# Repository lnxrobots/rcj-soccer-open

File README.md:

# RoboCup Soccer Open

## Setup

### Install packages and libraries

```
sudo apt install python3-pip git i2c-tools python3-opencv python3-serial python3-websockets
```

```
sudo pip3 install Adafruit-Blinka adafruit-circuitpython-bno055 adafruit-extended-bus adafruit-circuitpython-ssd1306 pillow bluedot
```

### Enable software I2C and second UART, disable builtin Bluetooth

Add following lines to `/boot/config.txt`:

```
# Software i2c - custom
dtoverlay=i2c-gpio,bus=3

# Second and fifth UART - custom
dtoverlay=uart2
dtoverlay=uart5

# Uncomment to disable builtin bluetooth - custom
#dtoverlay=disable-bt
```

### Pairing robots

Pair using [bluedot manual](https://bluedot.readthedocs.io/en/latest/pairpipi.html).

### Camera

Obtain frames using [Picamera2](https://github.com/raspberrypi/picamera2).

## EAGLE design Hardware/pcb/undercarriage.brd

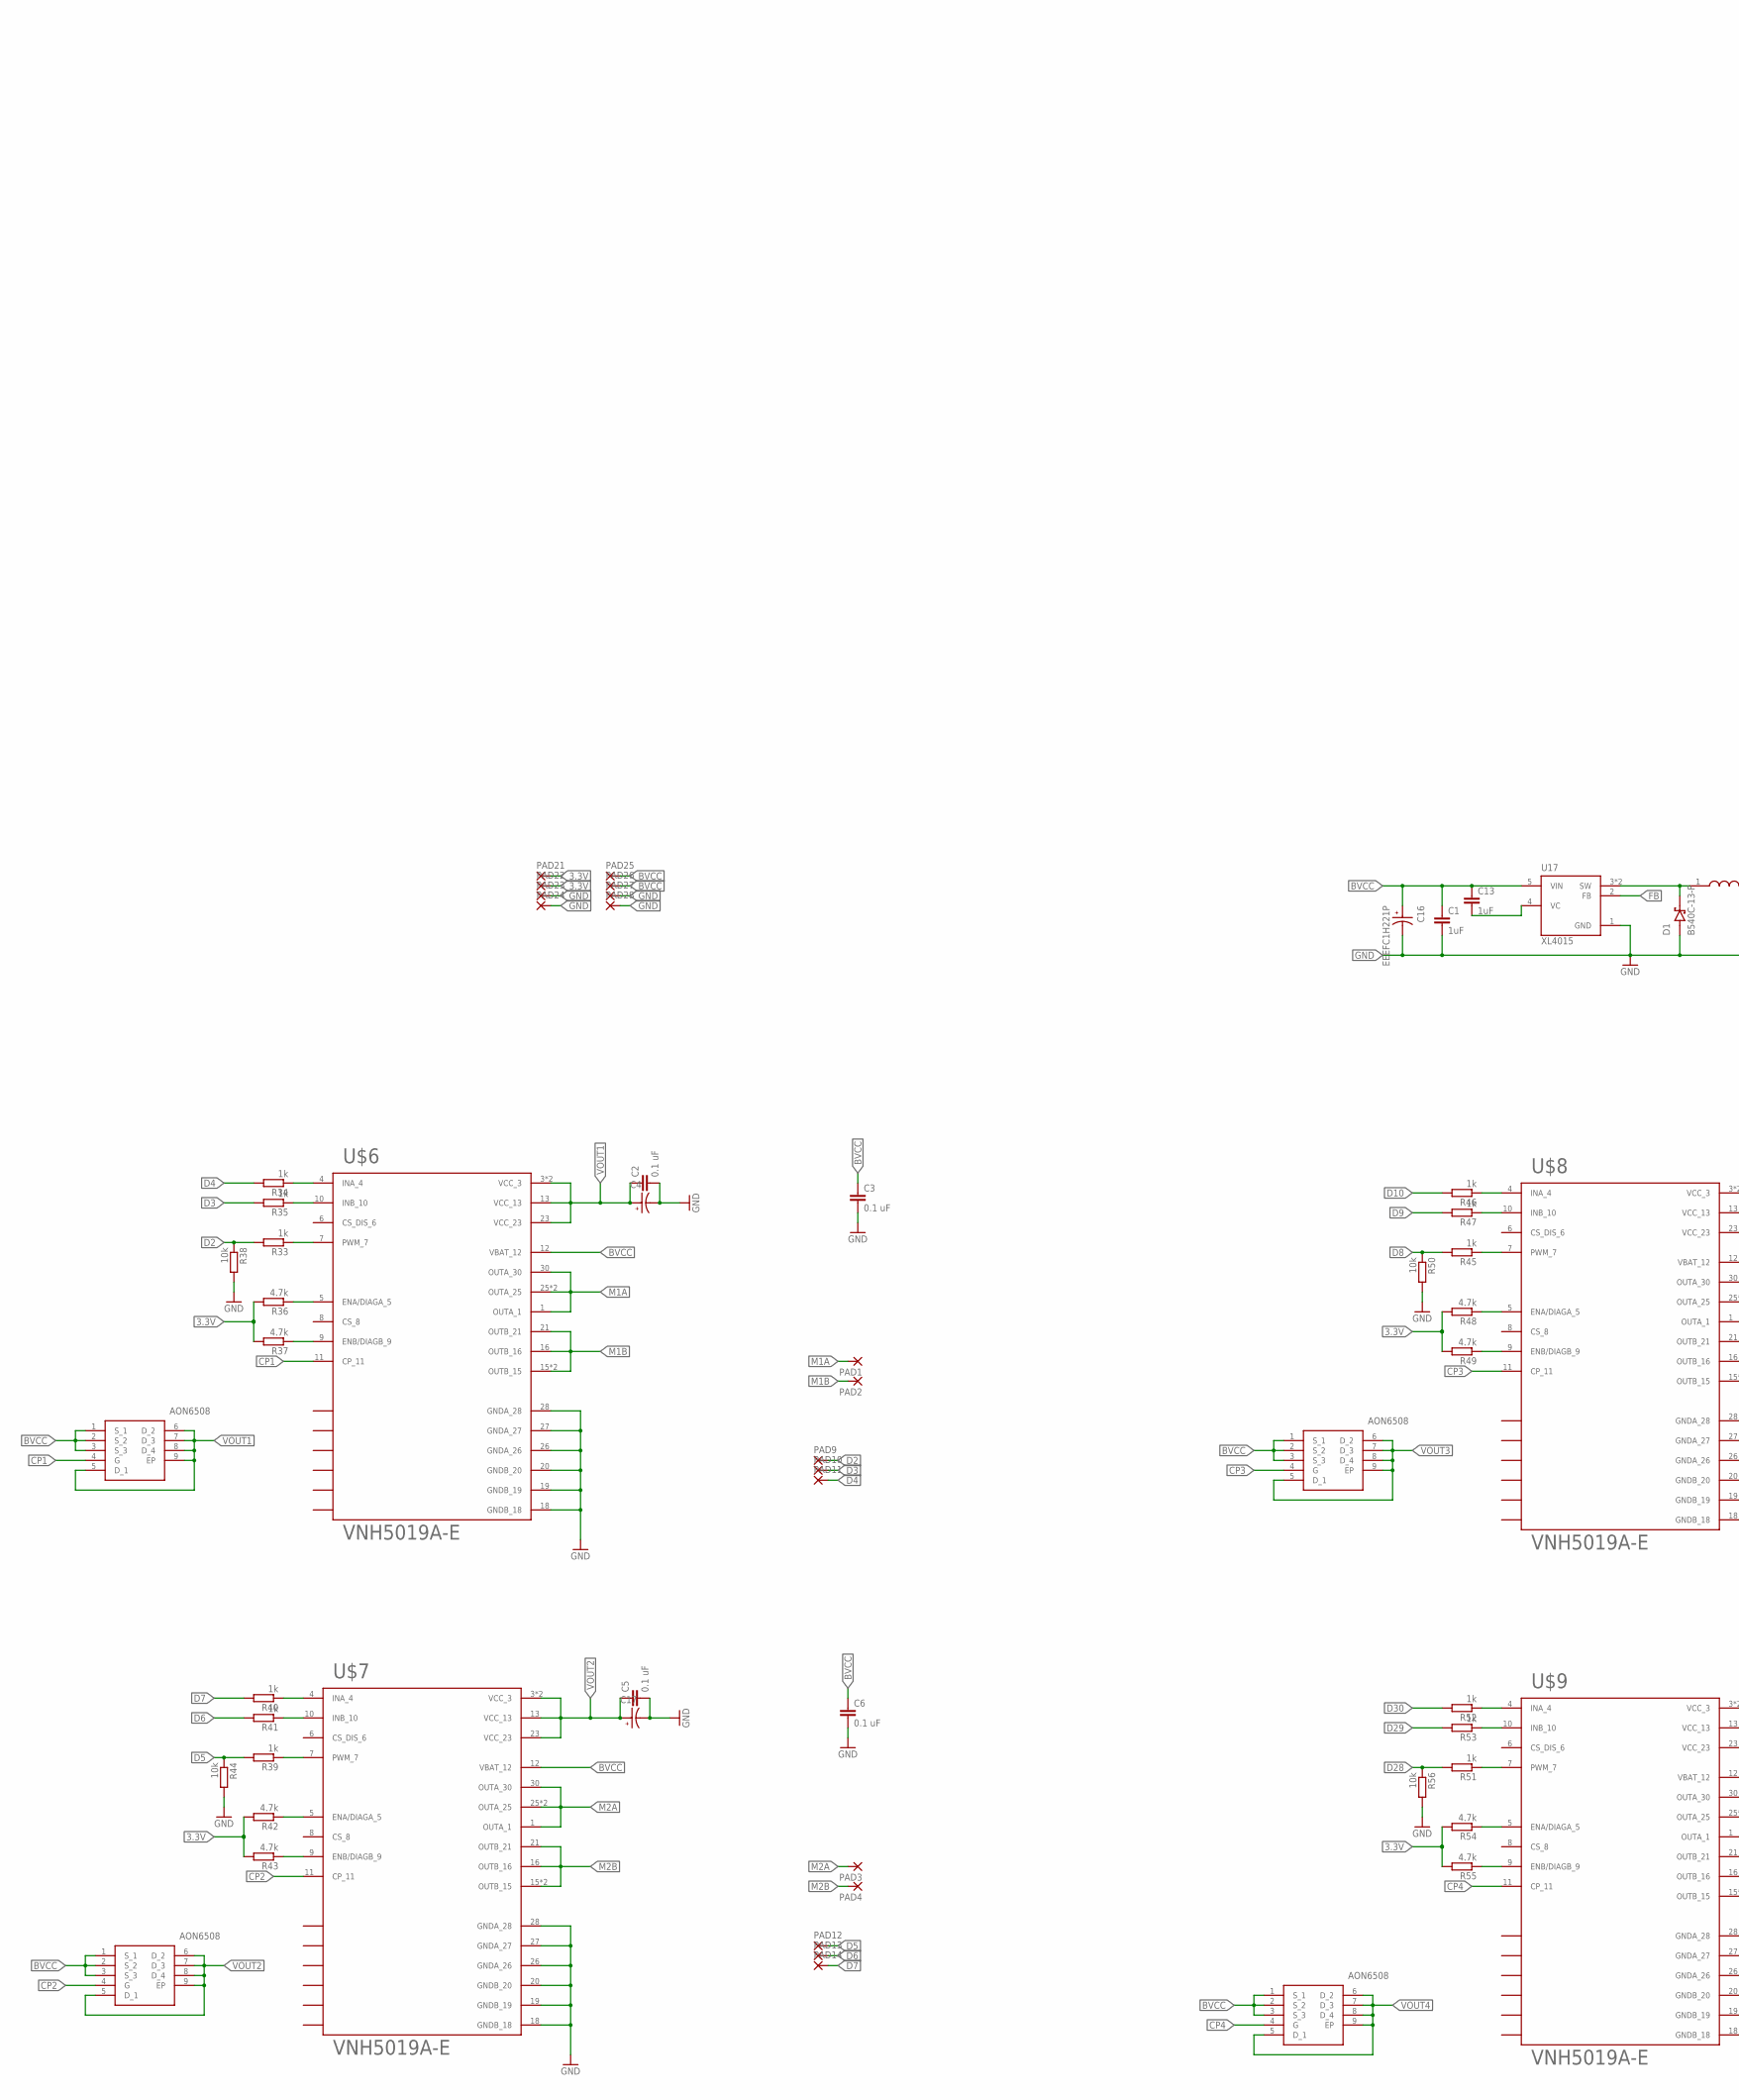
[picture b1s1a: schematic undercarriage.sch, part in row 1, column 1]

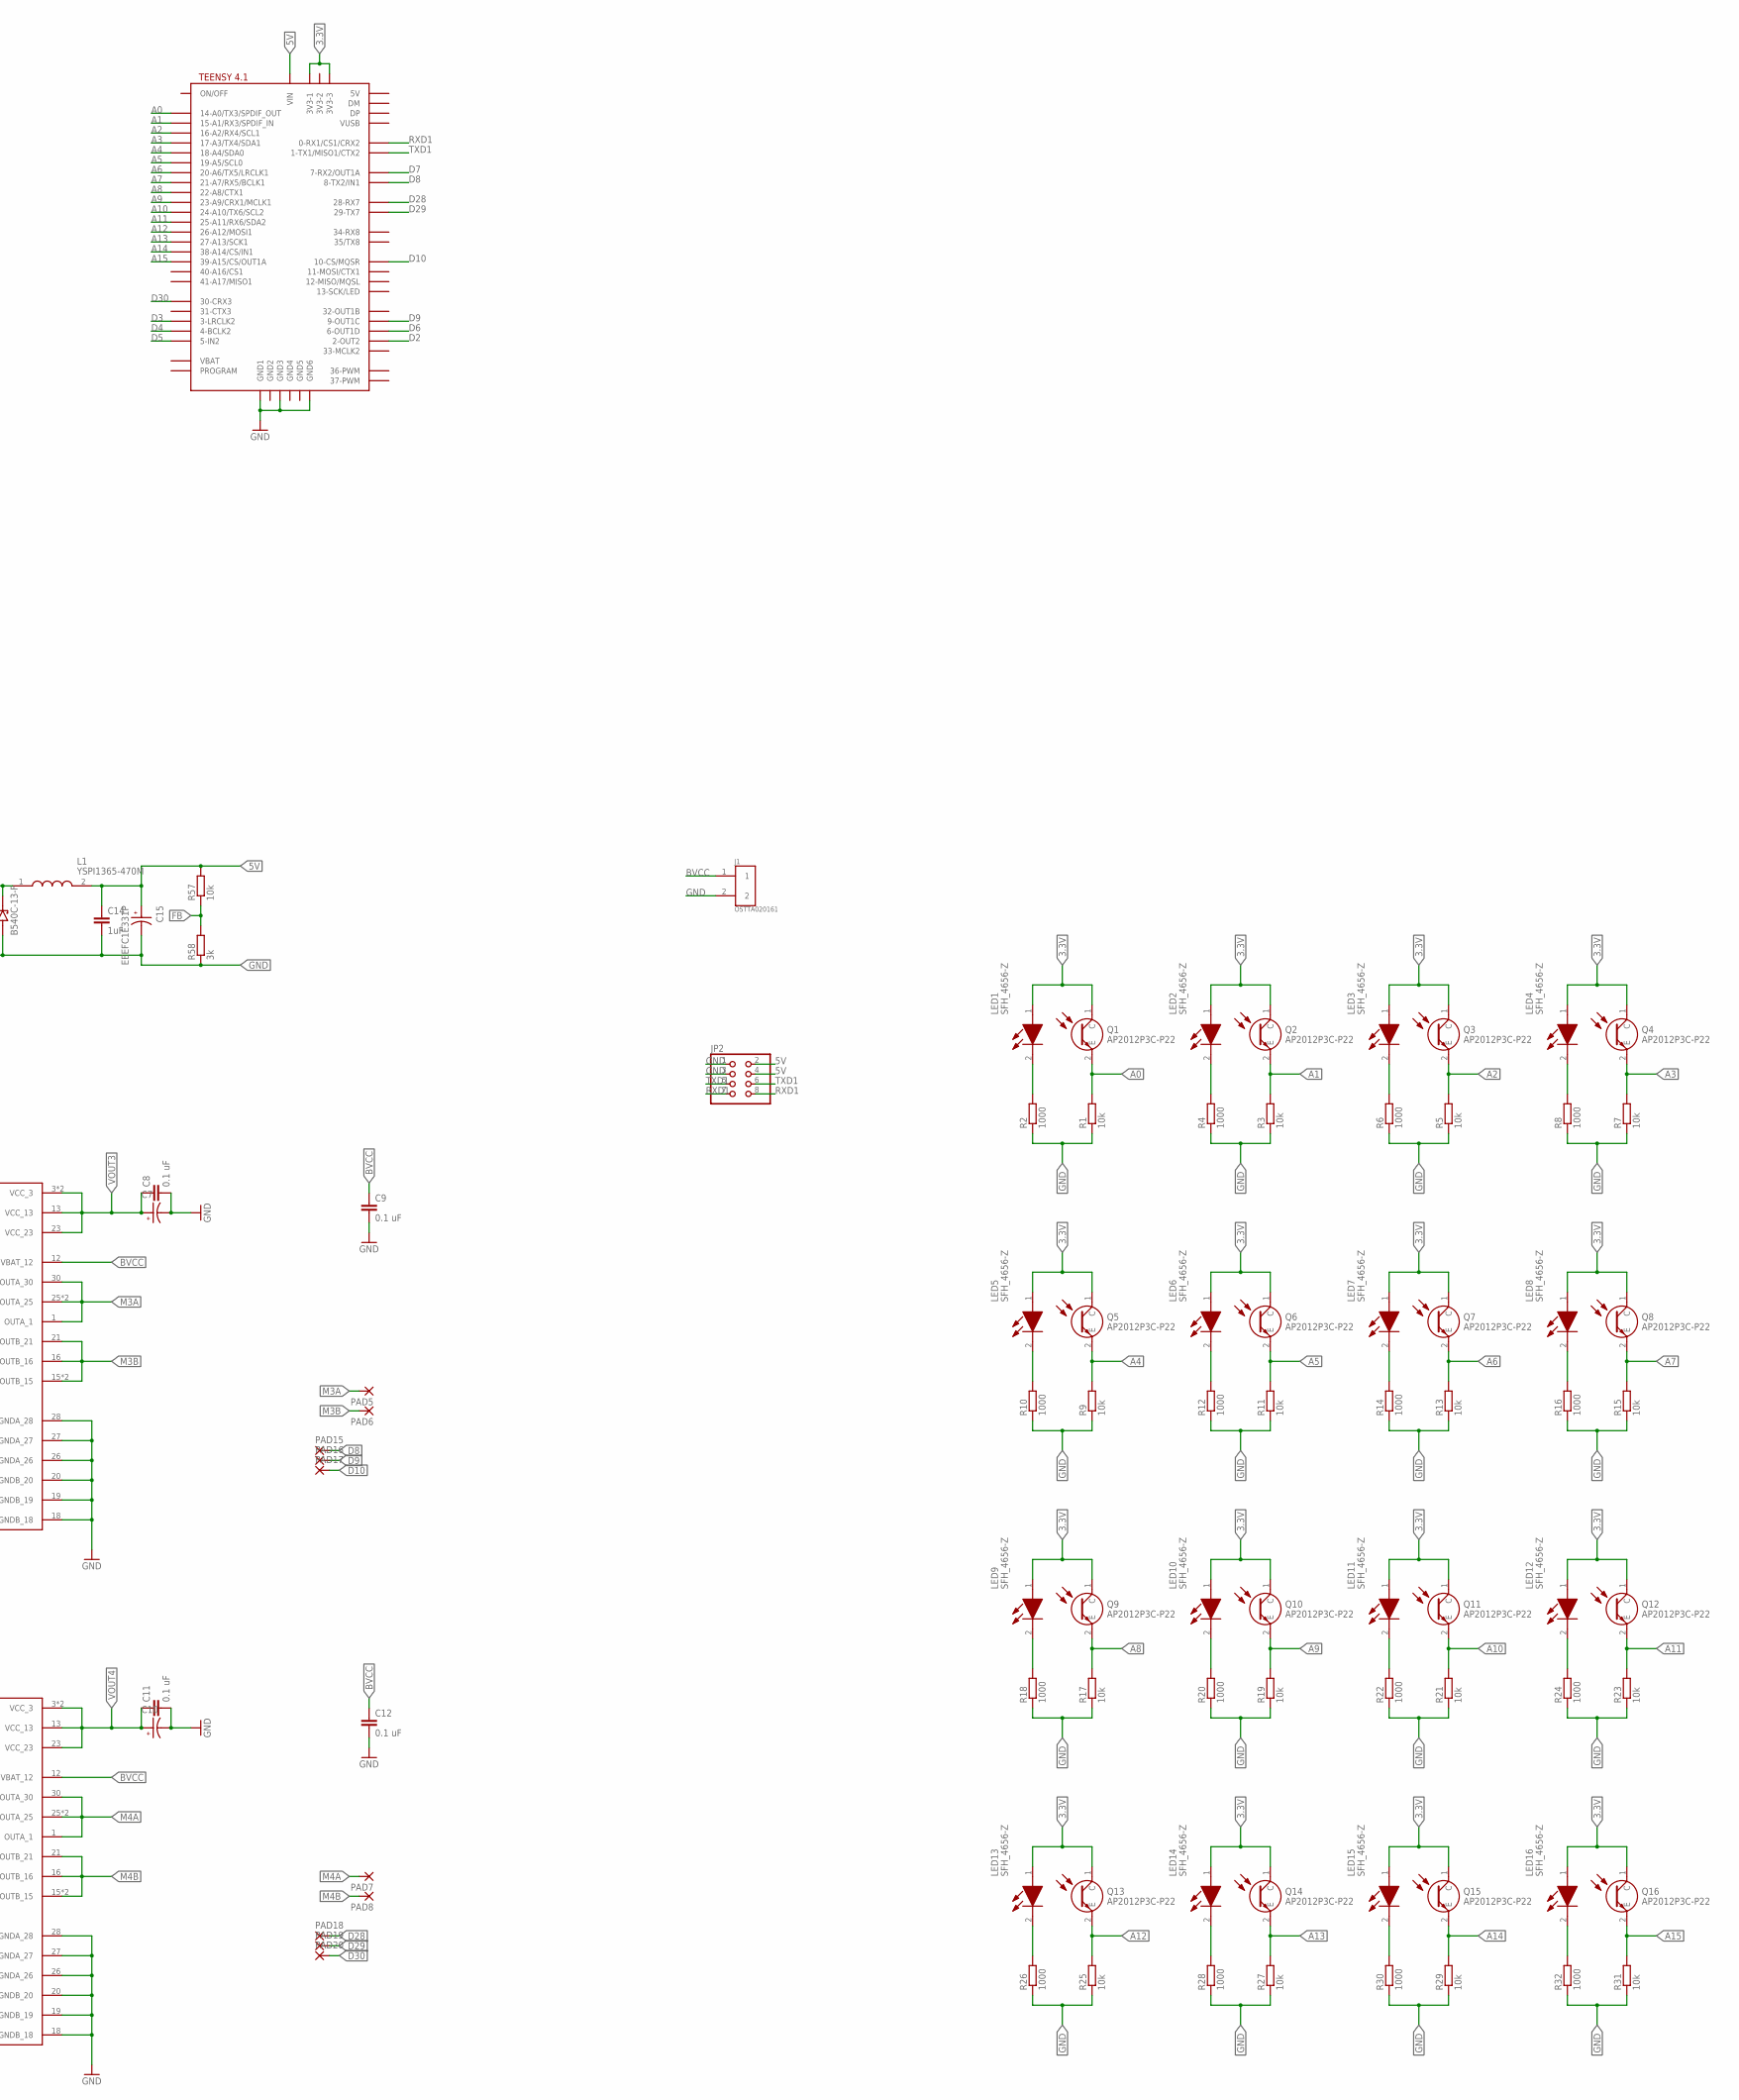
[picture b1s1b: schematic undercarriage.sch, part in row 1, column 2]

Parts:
C1, C13, C14: 1uF; C0603
C2, C3, C5, C6, C8, C9, C11, C12: 0.1 uF; C0603
C4, C7, C10, C17: EEEFT1H470AP; CAP_EEEFT1H470AP
C15: EEEFC1E331P; CAP_EEEFC1E331P
C16: EEEFC1H221P; CAP_EEEFC1H221P
D1: B540C-13-F; DIOM6959X245N
J1: OSTTA020161; OST_OSTTA020161
JP2: PINHD-2X4; 2X04
L1: YSPI1365-470M; INDPM138126X650N
LED1, LED2, LED3, LED4, LED5, LED6, LED7, LED8, LED9, LED10, LED11, LED12, LED13, LED14, LED15, LED16: SFH_4656-Z; SFH4656Z
PAD1, PAD2, PAD3, PAD4, PAD5, PAD6, PAD7, PAD8: 3,81/1,4
PAD9, PAD10, PAD11, PAD12, PAD13, PAD14, PAD15, PAD16, PAD17, PAD18, PAD19, PAD20, PAD21, PAD22, PAD23, PAD24: 1,6/0,9
PAD25, PAD26, PAD27, PAD28: 2,15/1,0
Q1, Q2, Q3, Q4, Q5, Q6, Q7, Q8, Q9, Q10, Q11, Q12, Q13, Q14, Q15, Q16: AP2012P3C-P22; AP2012P3CP22
Q17, Q18, Q19, Q20: AON6508
R1, R3, R5, R7, R9, R11, R13, R15, R17, R19, R21, R23, R25, R27, R29, R31, R38, R44, R50, R56, R57: 10k; R0603
R2, R4, R6, R8, R10, R12, R14, R16, R18, R20, R22, R24, R26, R28, R30, R32: 1000; R0603
R33, R34, R35, R39, R40, R41, R45, R46, R47, R51, R52, R53: 1k; R0603
R36, R37, R42, R43, R48, R49, R54, R55: 4.7k; R0603
R58: 3k; R0603
U17: XL4015; CONV_XL4015
U$5: TEENSY41-E; TENNSY41-E
U$6, U$7, U$8, U$9: VNH5019A-E; IC_MULTIPOWERSO-30TR

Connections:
3.3V: LED1.1 (A), LED2.1 (A), LED3.1 (A), LED4.1 (A), LED5.1 (A), LED6.1 (A), LED7.1 (A), LED8.1 (A), LED9.1 (A), LED10.1 (A), LED11.1 (A), LED12.1 (A), LED13.1 (A), LED14.1 (A), LED15.1 (A), LED16.1 (A), PAD21.1, PAD22.1, Q1.1 (C), Q2.1 (C), Q3.1 (C), Q4.1 (C), Q5.1 (C), Q6.1 (C), Q7.1 (C), Q8.1 (C), Q9.1 (C), Q10.1 (C), Q11.1 (C), Q12.1 (C), Q13.1 (C), Q14.1 (C), Q15.1 (C), Q16.1 (C), R36.2, R37.2, R42.2, R43.2, R48.2, R49.2, R54.2, R55.2, U$5.3V3-1, U$5.3V3-3
5V: C14.1, C15.1, JP2.2, JP2.4, L1.2, R57.2, U$5.VIN
A0: Q1.2 (E), R1.2, U$5.14-A0/TX3/SPDIF_OUT
A1: Q2.2 (E), R3.2, U$5.15-A1/RX3/SPDIF_IN
A2: Q3.2 (E), R5.2, U$5.16-A2/RX4/SCL1
A3: Q4.2 (E), R7.2, U$5.17-A3/TX4/SDA1
A4: Q5.2 (E), R9.2, U$5.18-A4/SDA0
A5: Q6.2 (E), R11.2, U$5.19-A5/SCL0
A6: Q7.2 (E), R13.2, U$5.20-A6/TX5/LRCLK1
A7: Q8.2 (E), R15.2, U$5.21-A7/RX5/BCLK1
A8: Q9.2 (E), R17.2, U$5.22-A8/CTX1
A9: Q10.2 (E), R19.2, U$5.23-A9/CRX1/MCLK1
A10: Q11.2 (E), R21.2, U$5.24-A10/TX6/SCL2
A11: Q12.2 (E), R23.2, U$5.25-A11/RX6/SDA2
A12: Q13.2 (E), R25.2, U$5.26-A12/MOSI1
A13: Q14.2 (E), R27.2, U$5.27-A13/SCK1
A14: Q15.2 (E), R29.2, U$5.38-A14/CS/IN1
A15: Q16.2 (E), R31.2, U$5.39-A15/CS/OUT1A
BVCC: C1.1, C3.1, C6.1, C9.1, C12.1, C13.1, C16.1, J1.1, PAD25.1, PAD26.1, Q17.1 (S_1), Q17.2 (S_2), Q17.3 (S_3), Q18.1 (S_1), Q18.2 (S_2), Q18.3 (S_3), Q19.1 (S_1), Q19.2 (S_2), Q19.3 (S_3), Q20.1 (S_1), Q20.2 (S_2), Q20.3 (S_3), U17.5 (VIN), U$6.12 (VBAT_12), U$7.12 (VBAT_12), U$8.12 (VBAT_12), U$9.12 (VBAT_12)
CP1: Q17.4 (G), U$6.11 (CP_11)
CP2: Q18.4 (G), U$7.11 (CP_11)
CP3: Q20.4 (G), U$8.11 (CP_11)
CP4: Q19.4 (G), U$9.11 (CP_11)
D2: PAD9.1, R33.2, R38.1, U$5.2-OUT2
D3: PAD10.1, R35.2, U$5.3-LRCLK2
D4: PAD11.1, R34.2, U$5.4-BCLK2
D5: PAD12.1, R39.2, R44.1, U$5.5-IN2
D6: PAD13.1, R41.2, U$5.6-OUT1D
D7: PAD14.1, R40.2, U$5.7-RX2/OUT1A
D8: PAD15.1, R45.2, R50.1, U$5.8-TX2/IN1
D9: PAD16.1, R47.2, U$5.9-OUT1C
D10: PAD17.1, R46.2, U$5.10-CS\MQSR (10-CS/MQSR)
D28: PAD18.1, R51.2, R56.1, U$5.28-RX7
D29: PAD19.1, R53.2, U$5.29-TX7
D30: PAD20.1, R52.2, U$5.30-CRX3
FB: R57.1, R58.2, U17.2 (FB)
GND: C1.2, C2.2, C3.2, C4.2, C5.2, C6.2, C7.2, C8.2, C9.2, C10.2, C11.2, C12.2, C14.2, C15.2, C16.2, C17.2, D1.A, J1.2, JP2.1, JP2.3, PAD23.1, PAD24.1, PAD27.1, PAD28.1, R1.1, R2.1, R3.1, R4.1, R5.1, R6.1, R7.1, R8.1, R9.1, R10.1, R11.1, R12.1, R13.1, R14.1, R15.1, R16.1, R17.1, R18.1, R19.1, R20.1, R21.1, R22.1, R23.1, R24.1, R25.1, R26.1, R27.1, R28.1, R29.1, R30.1, R31.1, R32.1, R38.2, R44.2, R50.2, R56.2, R58.1, U17.1 (GND), U$5.GND1, U$5.GND3, U$5.GND6, U$6.18 (GNDB_18), U$6.19 (GNDB_19), U$6.20 (GNDB_20), U$6.26 (GNDA_26), U$6.27 (GNDA_27), U$6.28 (GNDA_28), U$7.18 (GNDB_18), U$7.19 (GNDB_19), U$7.20 (GNDB_20), U$7.26 (GNDA_26), U$7.27 (GNDA_27), U$7.28 (GNDA_28), U$8.18 (GNDB_18), U$8.19 (GNDB_19), U$8.20 (GNDB_20), U$8.26 (GNDA_26), U$8.27 (GNDA_27), U$8.28 (GNDA_28), U$9.18 (GNDB_18), U$9.19 (GNDB_19), U$9.20 (GNDB_20), U$9.26 (GNDA_26), U$9.27 (GNDA_27), U$9.28 (GNDA_28)
M1A: PAD1.1, U$6.1 (OUTA_1), U$6.25 (OUTA_25), U$6.30 (OUTA_30), U$6.HS2 (OUTA_25)
M1B: PAD2.1, U$6.15 (OUTB_15), U$6.16 (OUTB_16), U$6.21 (OUTB_21), U$6.HS3 (OUTB_15)
M2A: PAD3.1, U$7.1 (OUTA_1), U$7.25 (OUTA_25), U$7.30 (OUTA_30), U$7.HS2 (OUTA_25)
M2B: PAD4.1, U$7.15 (OUTB_15), U$7.16 (OUTB_16), U$7.21 (OUTB_21), U$7.HS3 (OUTB_15)
M3A: PAD5.1, U$8.1 (OUTA_1), U$8.25 (OUTA_25), U$8.30 (OUTA_30), U$8.HS2 (OUTA_25)
M3B: PAD6.1, U$8.15 (OUTB_15), U$8.16 (OUTB_16), U$8.21 (OUTB_21), U$8.HS3 (OUTB_15)
M4A: PAD7.1, U$9.1 (OUTA_1), U$9.25 (OUTA_25), U$9.30 (OUTA_30), U$9.HS2 (OUTA_25)
M4B: PAD8.1, U$9.15 (OUTB_15), U$9.16 (OUTB_16), U$9.21 (OUTB_21), U$9.HS3 (OUTB_15)
unnamed: LED2.2 (K), R4.2
unnamed: LED3.2 (K), R6.2
unnamed: LED1.2 (K), R2.2
unnamed: LED4.2 (K), R8.2
unnamed: R33.1, U$6.7 (PWM_7)
unnamed: R34.1, U$6.4 (INA_4)
unnamed: C13.2, U17.4 (VC)
unnamed: R35.1, U$6.10 (INB_10)
unnamed: LED5.2 (K), R10.2
unnamed: LED6.2 (K), R12.2
unnamed: R37.1, U$6.9 (ENB/DIAGB_9)
unnamed: R36.1, U$6.5 (ENA/DIAGA_5)
unnamed: R39.1, U$7.7 (PWM_7)
unnamed: R40.1, U$7.4 (INA_4)
unnamed: R41.1, U$7.10 (INB_10)
unnamed: R43.1, U$7.9 (ENB/DIAGB_9)
unnamed: LED7.2 (K), R14.2
unnamed: LED8.2 (K), R16.2
unnamed: LED9.2 (K), R18.2
unnamed: LED10.2 (K), R20.2
unnamed: LED11.2 (K), R22.2
unnamed: LED12.2 (K), R24.2
unnamed: LED13.2 (K), R26.2
unnamed: LED14.2 (K), R28.2
unnamed: LED15.2 (K), R30.2
unnamed: LED16.2 (K), R32.2
unnamed: R42.1, U$7.5 (ENA/DIAGA_5)
unnamed: R45.1, U$8.7 (PWM_7)
unnamed: R46.1, U$8.4 (INA_4)
unnamed: R47.1, U$8.10 (INB_10)
unnamed: R49.1, U$8.9 (ENB/DIAGB_9)
unnamed: R48.1, U$8.5 (ENA/DIAGA_5)
unnamed: R51.1, U$9.7 (PWM_7)
unnamed: R52.1, U$9.4 (INA_4)
unnamed: R53.1, U$9.10 (INB_10)
unnamed: R55.1, U$9.9 (ENB/DIAGB_9)
unnamed: R54.1, U$9.5 (ENA/DIAGA_5)
unnamed: D1.C (K), L1.1, U17.3 (SW), U17.3.1 (SW)
RXD1: JP2.7, JP2.8, U$5.0-RX1/CS1/CRX2
TXD1: JP2.5, JP2.6, U$5.1-TX1/MISO1/CTX2
VOUT1: C2.1, C4.1, Q17.5 (D_1), Q17.6 (D_2), Q17.7 (D_3), Q17.8 (D_4), Q17.9 (EP), U$6.3 (VCC_3), U$6.13 (VCC_13), U$6.23 (VCC_23), U$6.HS1 (VCC_3)
VOUT2: C5.1, C17.1, Q18.5 (D_1), Q18.6 (D_2), Q18.7 (D_3), Q18.8 (D_4), Q18.9 (EP), U$7.3 (VCC_3), U$7.13 (VCC_13), U$7.23 (VCC_23), U$7.HS1 (VCC_3)
VOUT3: C7.1, C8.1, Q20.5 (D_1), Q20.6 (D_2), Q20.7 (D_3), Q20.8 (D_4), Q20.9 (EP), U$8.3 (VCC_3), U$8.13 (VCC_13), U$8.23 (VCC_23), U$8.HS1 (VCC_3)
VOUT4: C10.1, C11.1, Q19.5 (D_1), Q19.6 (D_2), Q19.7 (D_3), Q19.8 (D_4), Q19.9 (EP), U$9.3 (VCC_3), U$9.13 (VCC_13), U$9.23 (VCC_23), U$9.HS1 (VCC_3)

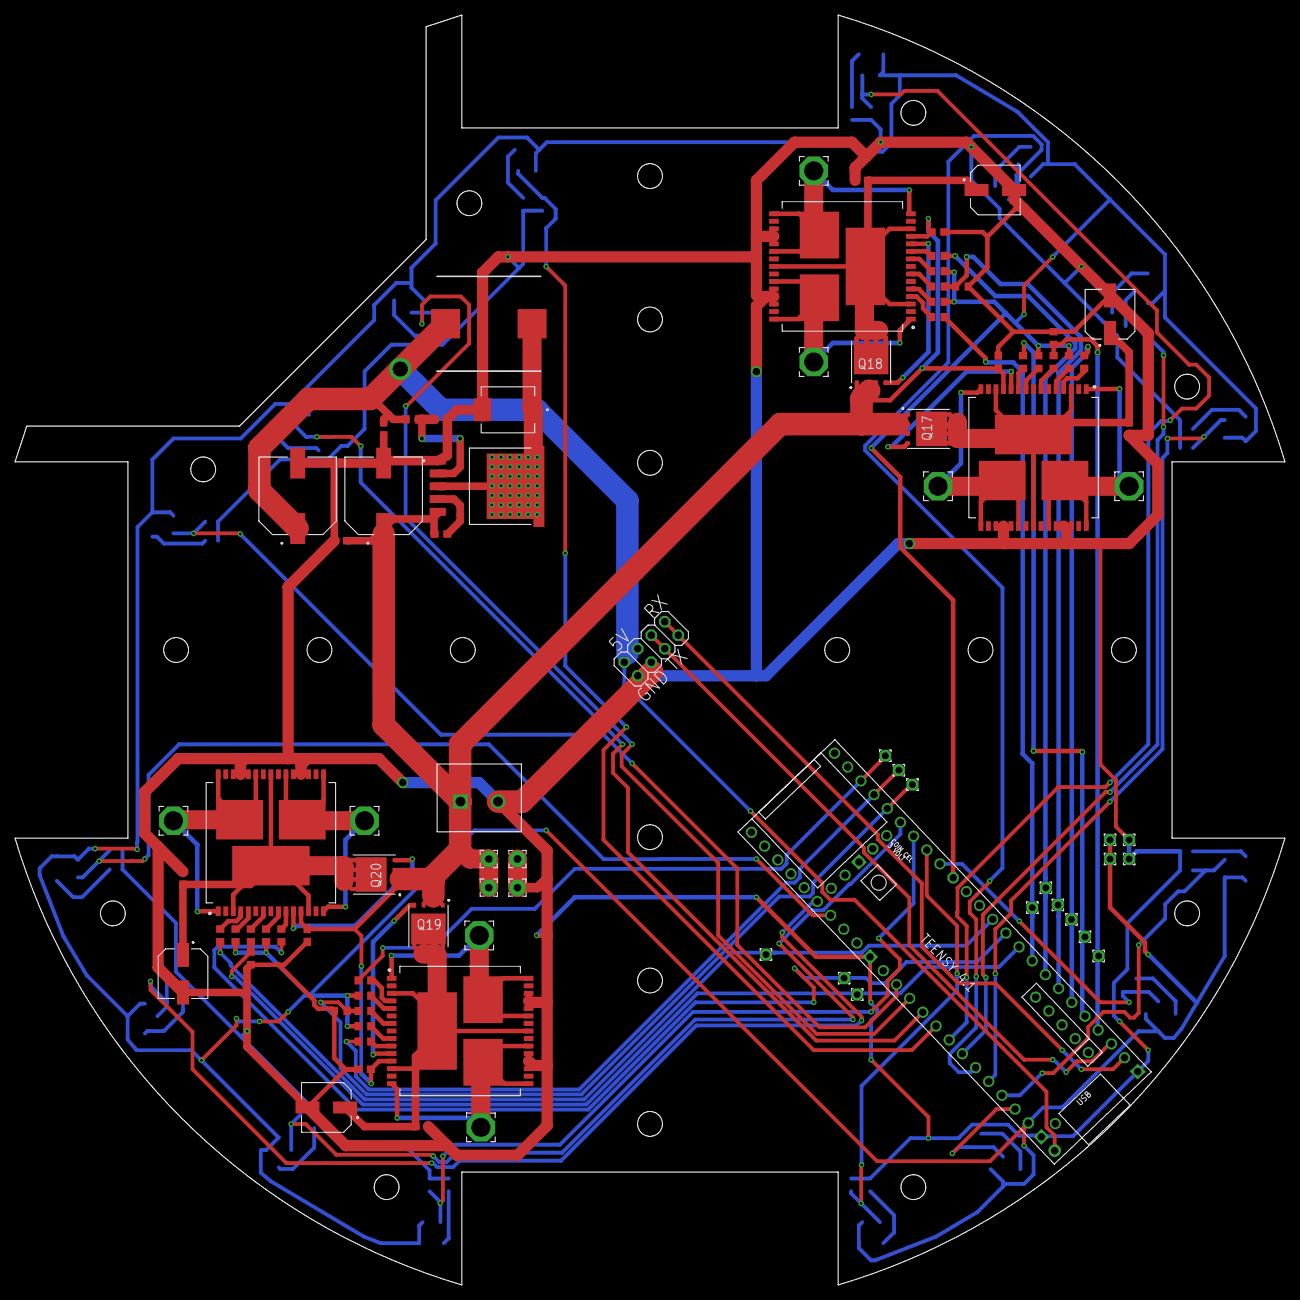
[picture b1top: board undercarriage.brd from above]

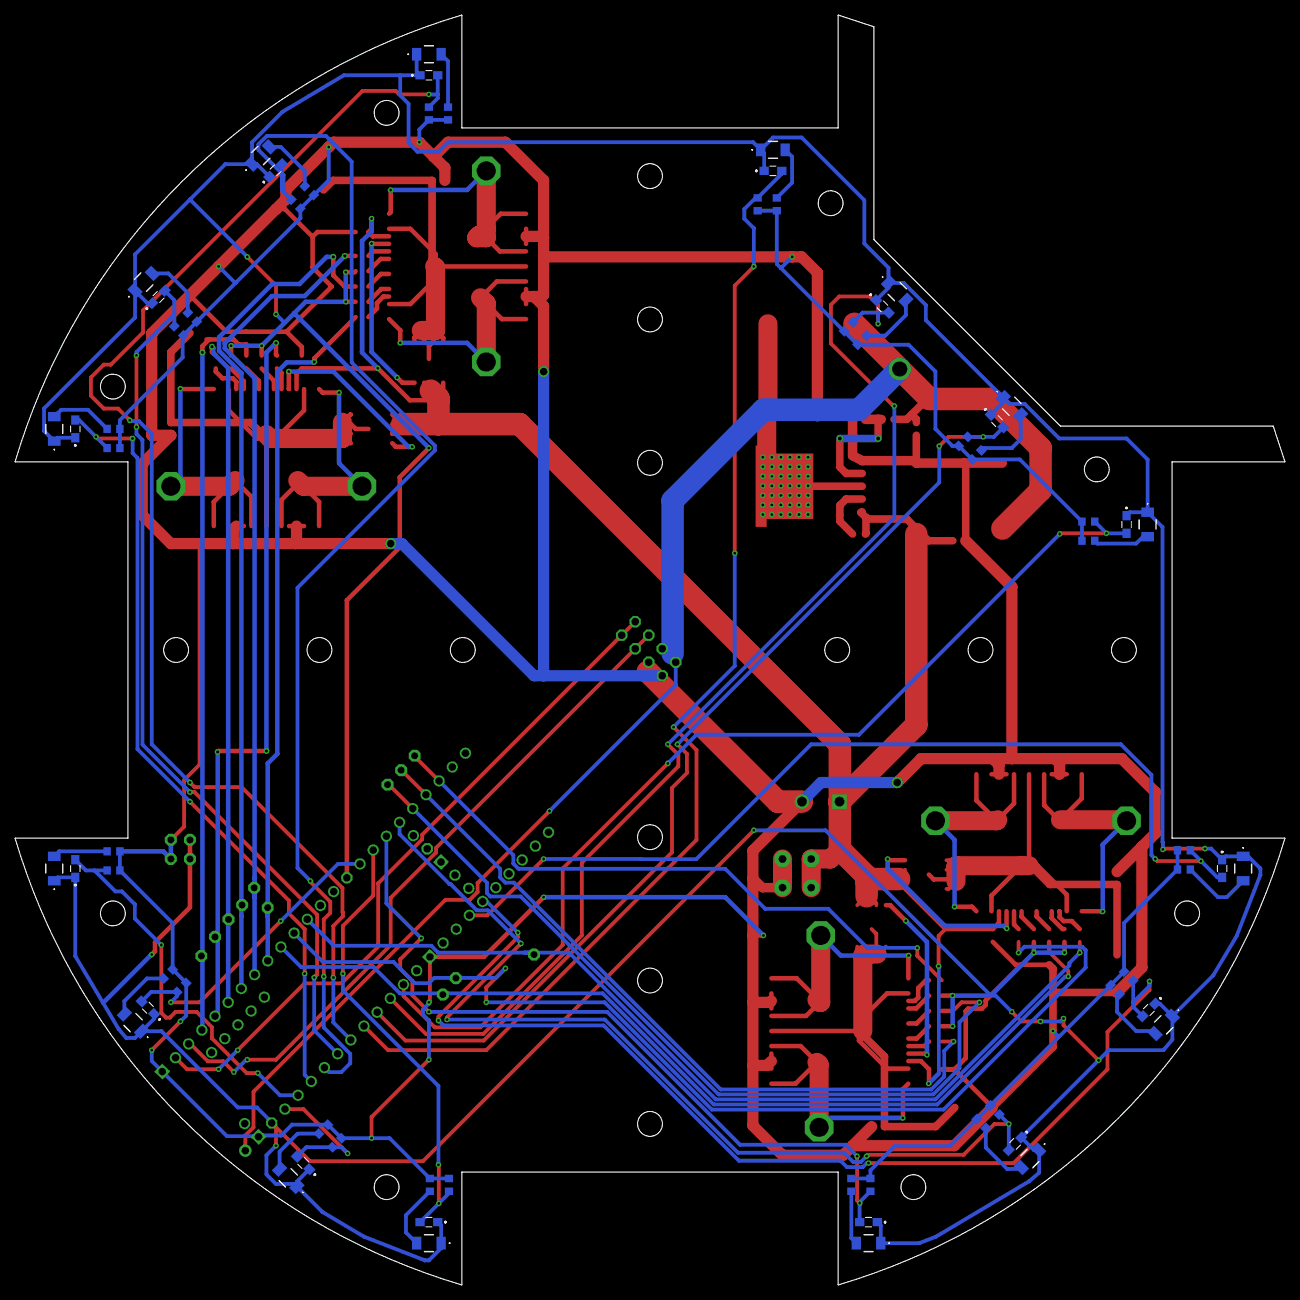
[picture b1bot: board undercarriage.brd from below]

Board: 2 copper layers, 168.7 x 168.7 mm, 149 parts (64 on the bottom side), 89 nets.

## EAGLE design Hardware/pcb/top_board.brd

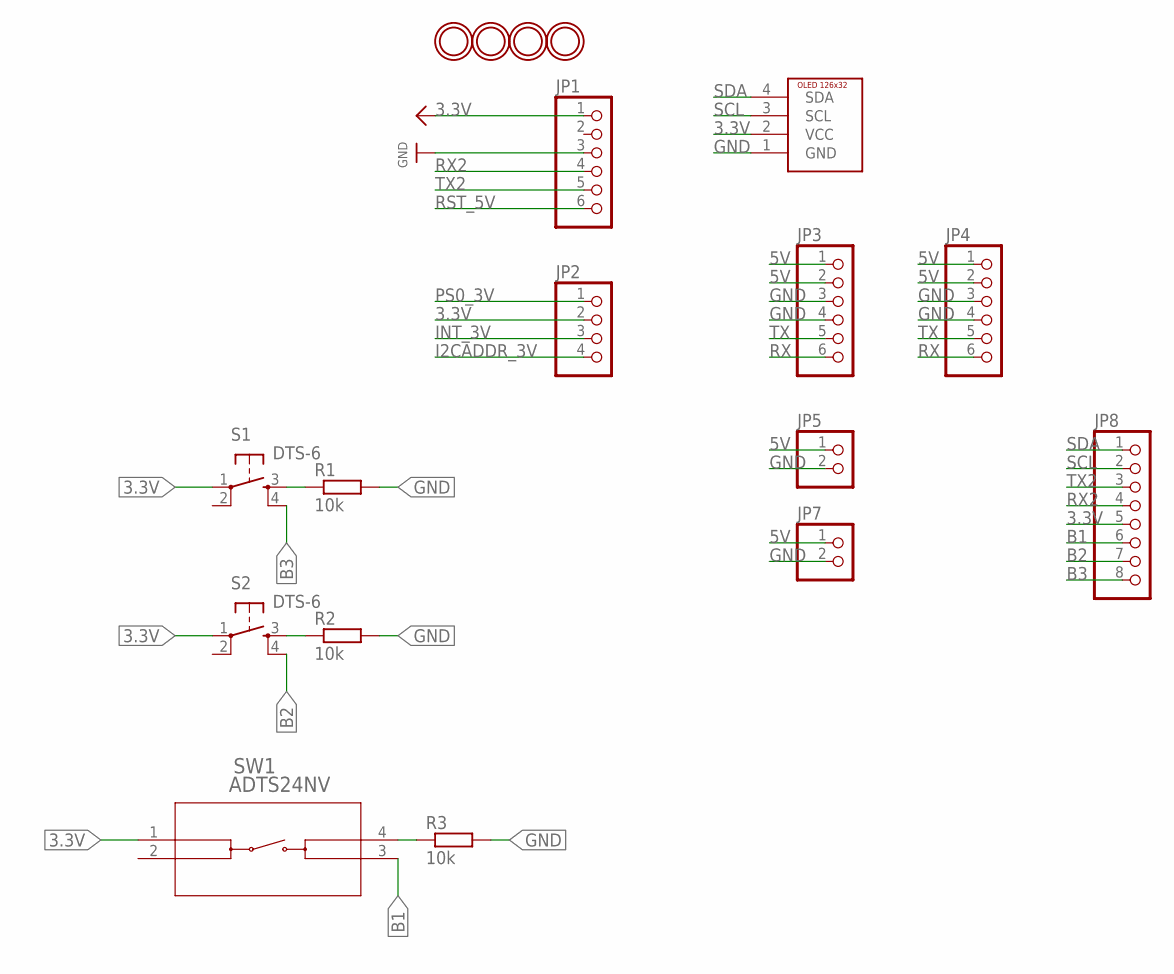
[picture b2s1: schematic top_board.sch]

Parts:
JP1: HEADER-1X676MIL; 1X06_ROUND_76
JP2: HEADER-1X476MIL; 1X04_ROUND_76
JP3, JP4: PINHD-1X6; 1X06
JP5, JP7: PINHD-1X2; 1X02
JP8: PINHD-1X8; 1X08
R1, R2, R3: 10k; R0603
S1, S2: DTS-6
SW1: ADTS24NV; ADTS24*V_APM
U$1: OLED126X32THROUGH_HOLE; OLED128X64
U$29, U$30, U$31, U$32: MOUNTINGHOLE2.5_THICK; MOUNTINGHOLE_2.5_PLATED_THICK

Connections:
3.3V: JP1.1, JP2.2, JP8.5, S1.1, S2.1, SW1.1, U$1.2 (VCC)
5V: JP3.1, JP3.2, JP4.1, JP4.2, JP5.1, JP7.1
B1: JP8.6, SW1.3
B2: JP8.7, S2.4
B3: JP8.8, S1.4
GND: JP1.3, JP3.3, JP3.4, JP4.3, JP4.4, JP5.2, JP7.2, R1.2, R2.2, R3.2, U$1.1 (GND)
I2CADDR_3V: JP2.4
INT_3V: JP2.3
unnamed: R1.1, S1.3
unnamed: R2.1, S2.3
unnamed: R3.1, SW1.4
PS0_3V: JP2.1
RST_5V: JP1.6
RX: JP3.6, JP4.6
RX2: JP1.4, JP8.4
SCL: JP8.2, U$1.3 (SCL)
SDA: JP8.1, U$1.4 (SDA)
TX: JP3.5, JP4.5
TX2: JP1.5, JP8.3

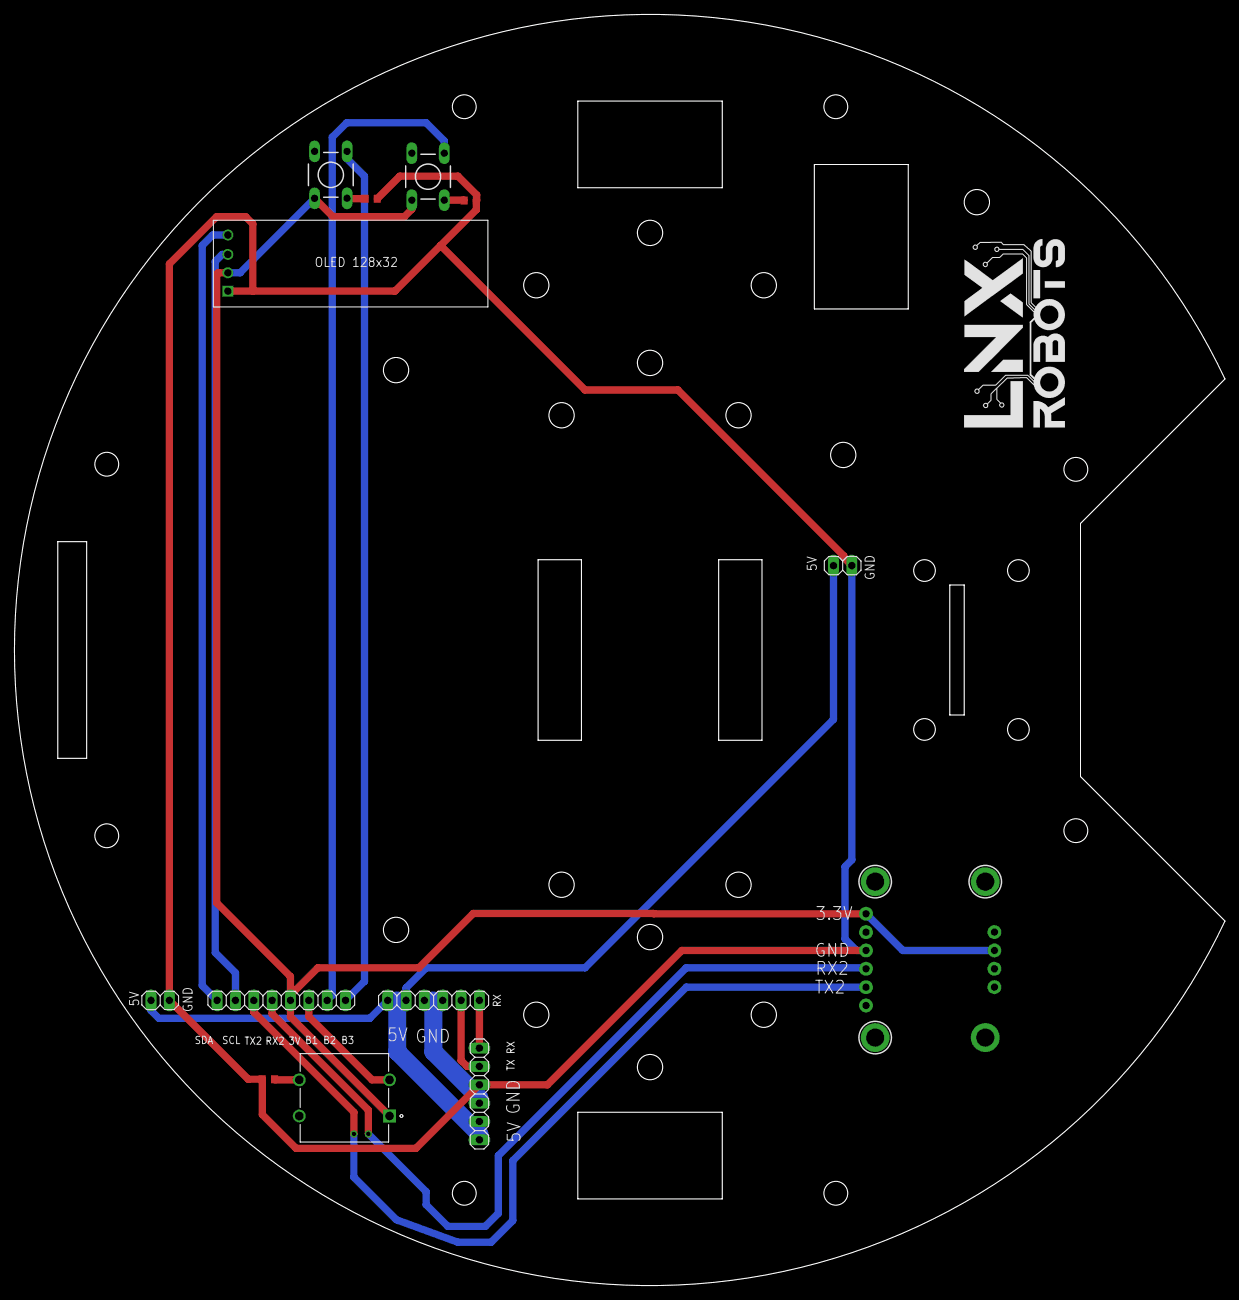
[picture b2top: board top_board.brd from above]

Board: 2 copper layers, 167.6 x 176.0 mm, 18 parts (1 on the bottom side), 15 nets.

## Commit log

2023-08-07 RoboCup 2023 Bordeaux update

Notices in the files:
parts and their libraries:
microbuilder: This work is placed in the public domain, and may be freely used for commercial and non-commercial work with the following conditions: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
COPYRIGHT: Copyright (C) 2023 Ultra Librarian. All rights reserved.
